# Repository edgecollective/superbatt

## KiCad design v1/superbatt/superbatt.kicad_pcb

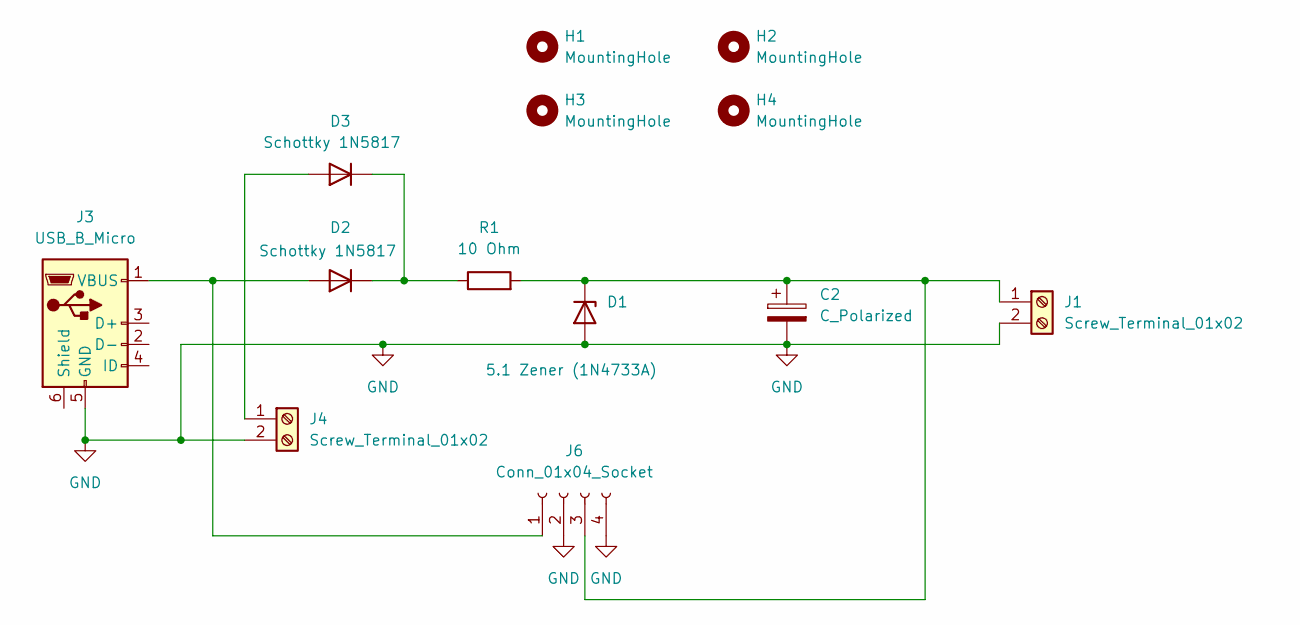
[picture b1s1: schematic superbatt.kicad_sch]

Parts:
C2: C_Polarized; CP_Radial_D22.0mm_P5.00mm_SnapIn
D1: 5.1 Zener (1N4733A); D_DO-41_SOD81_P10.16mm_Horizontal
D2, D3: Schottky 1N5817; D_DO-41_SOD81_P10.16mm_Horizontal
H1, H2, H3, H4: MountingHole; MountingHole_3.2mm_M3
J1, J4: Screw_Terminal_01x02; TerminalBlock_Phoenix_MKDS-1,5-2-5.08_1x02_P5.08mm_Horizont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
J3: USB_B_Micro; USB_Micro-B_Wuerth_629105150521
J6: Conn_01x04_Socket; PinSocket_1x04_P2.54mm_Vertical
R1: 10 Ohm; R_Axial_DIN0207_L6.3mm_D2.5mm_P10.16mm_Horizontal

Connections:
GND: C2.2, D1.2 (A), J1.2, J3.5 (GND), J4.2, J6.2, J6.4
unnamed: C2.1, D1.1 (K), J1.1, J6.3, R1.2
unnamed: D2.2 (A), J3.1 (VBUS), J6.1
unnamed: D2.1 (K), D3.1 (K), R1.1
unnamed: D3.2 (A), J4.1

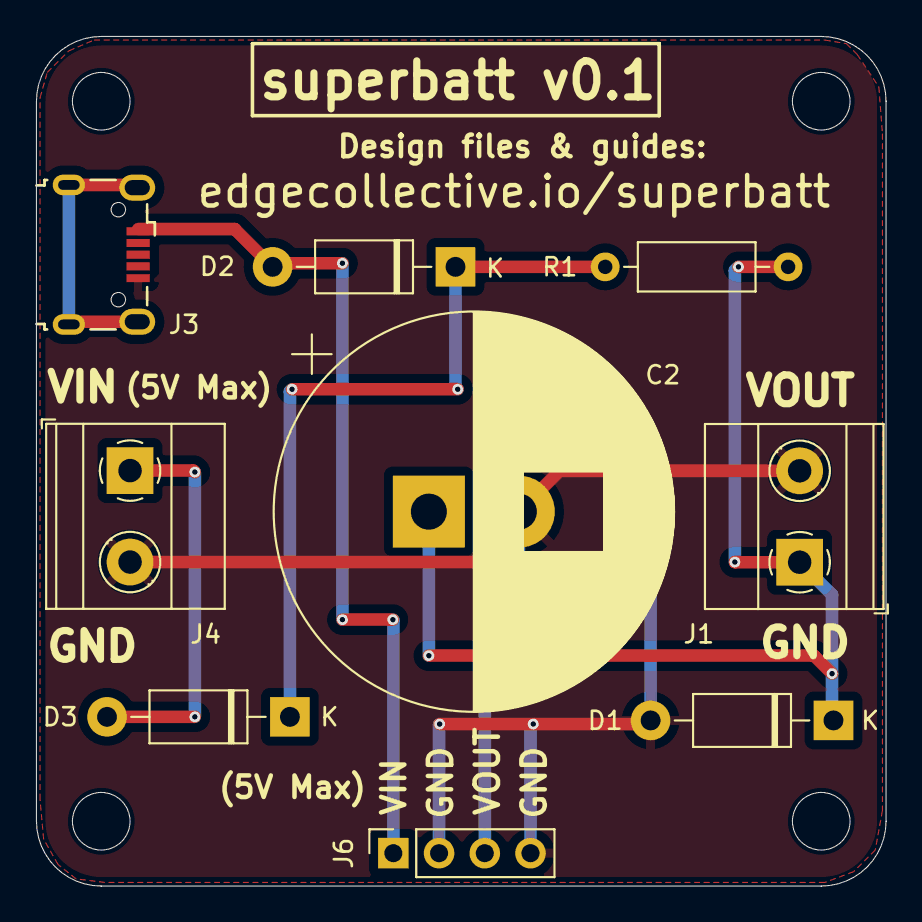
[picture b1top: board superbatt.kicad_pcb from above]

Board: 2 copper layers, 47.2 x 47.2 mm, 13 parts (0 on the bottom side), 5 nets.
